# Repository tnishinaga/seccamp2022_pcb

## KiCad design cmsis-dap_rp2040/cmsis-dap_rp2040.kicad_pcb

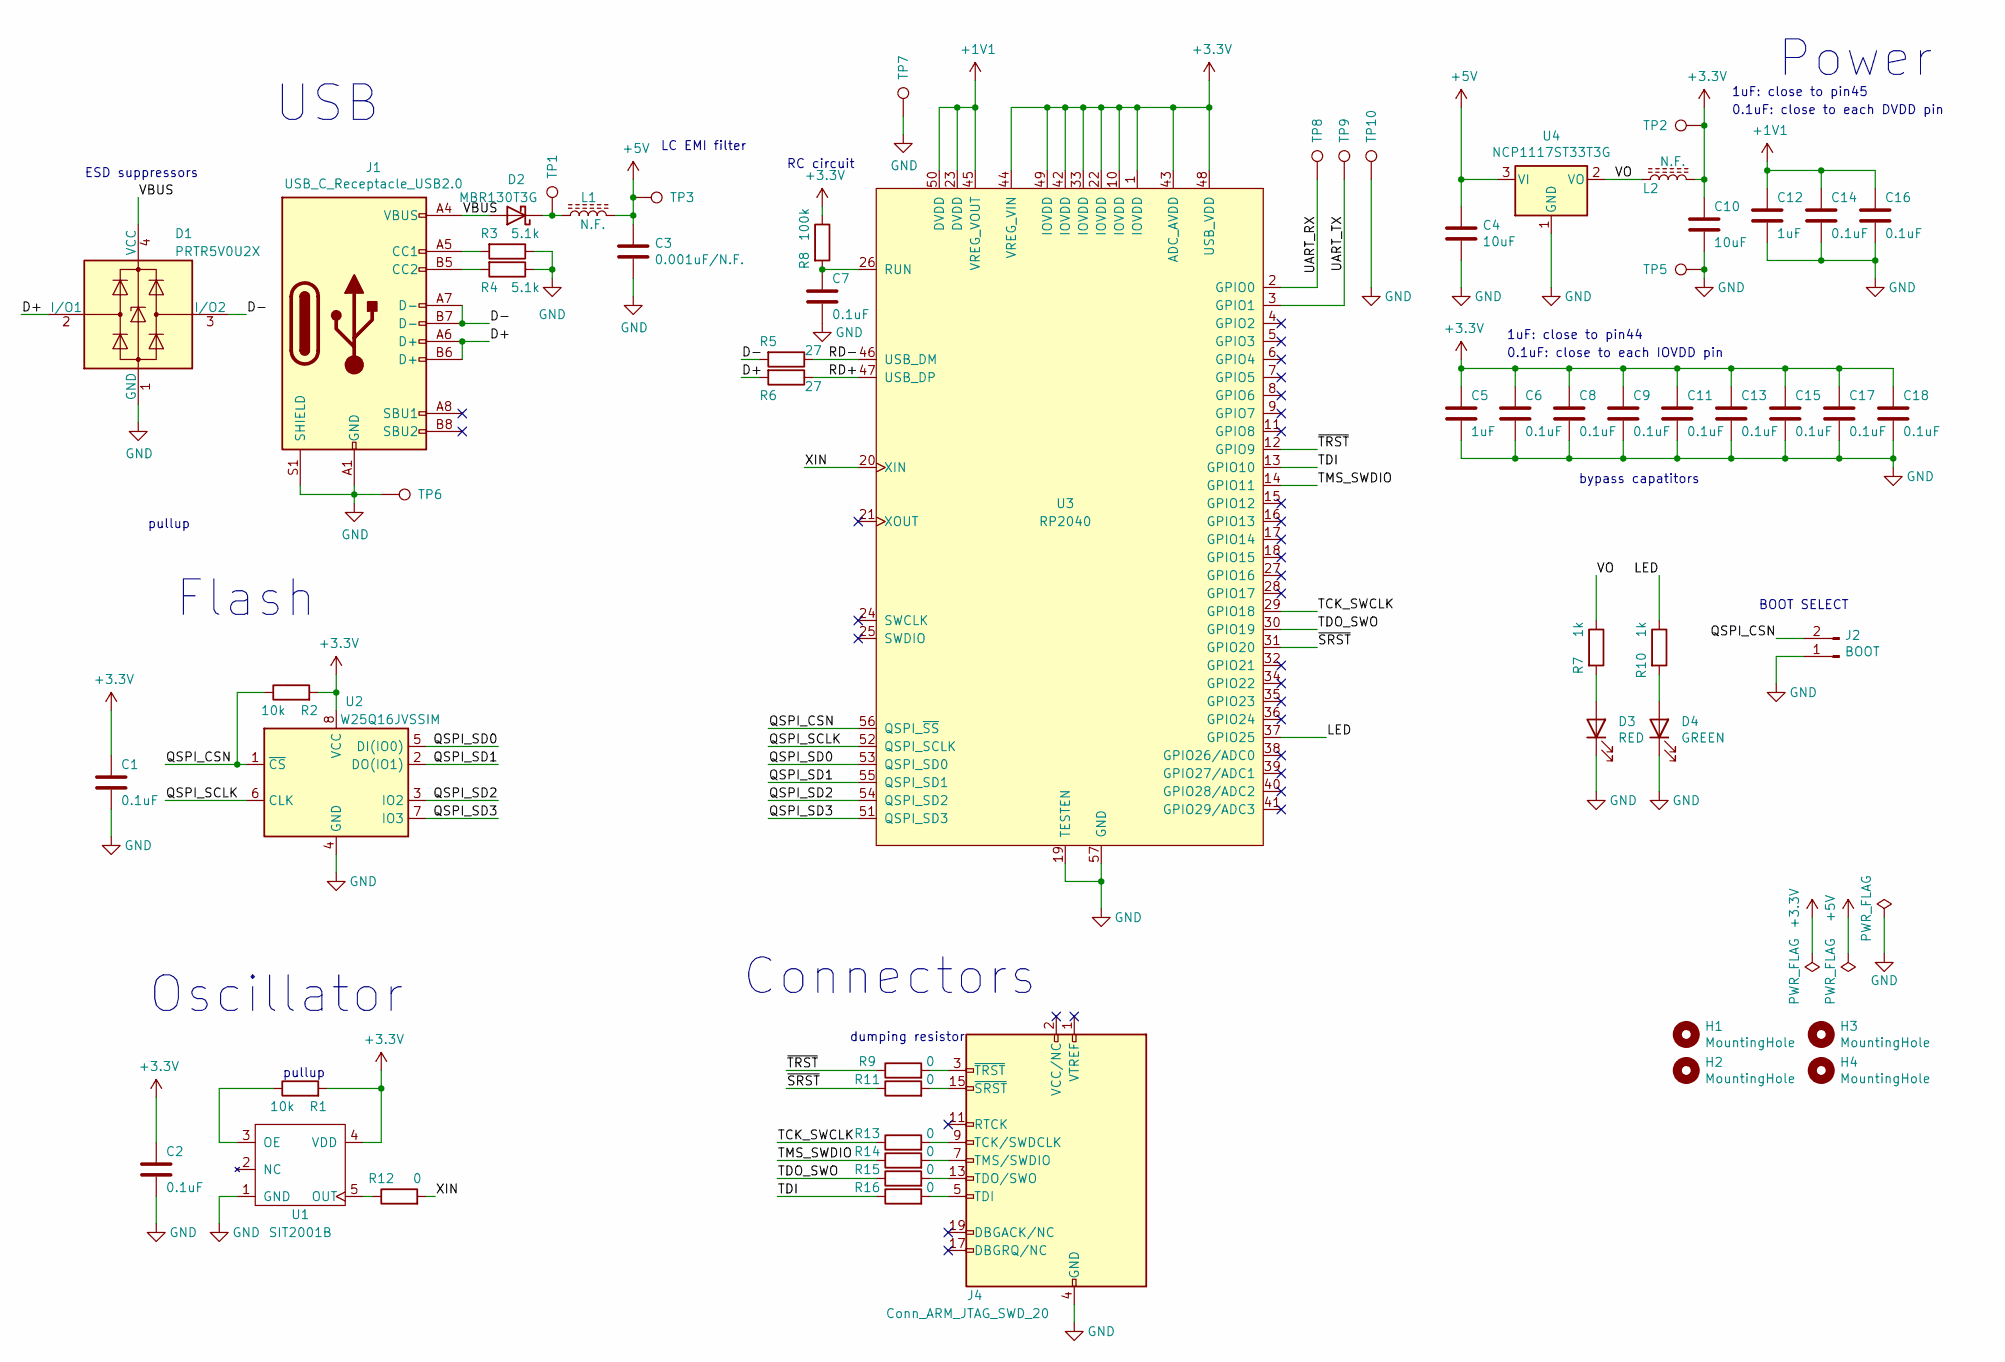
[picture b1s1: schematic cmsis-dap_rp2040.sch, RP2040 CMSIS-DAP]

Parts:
C1, C2, C6, C7, C8, C9, C11, C13, C14, C15, C16, C17, C18: 0.1uF; C_0603_1608Metric; MPN C1608X7R1E104M080AA
C3: 0.001uF/N.F.; C_0603_1608Metric; MPN CL10C102JB8NNND
C4, C10: 10uF; C_0603_1608Metric; MPN CL10A106MQ8NNNC
C5, C12: 1uF; C_0603_1608Metric; MPN C0603C105K8PACTU
D1: PRTR5V0U2X; SOT-143; MPN PRTR5V0U2X
D2: MBR130T3G; D_SOD-123F; MPN MBR130T3G
D3: RED; D_0603_1608Metric; MPN OSR50603C1E
D4: GREEN; D_0603_1608Metric; MPN OSG50603C1E
H1, H2, H3, H4: MountingHole; MountingHole_3mm
J1: USB_C_Receptacle_USB2.0; USB_C_Receptacle_GCT_USB4085; MPN USB4085-GF-A
J2: BOOT; PinHeader_1x02_P2.54mm_Vertical
J4: Conn_ARM_JTAG_SWD_20; IDC-Header_2x10_P2.54mm_Vertical
L1, L2: N.F.; L_0603_1608Metric; MPN BLM18AG601SN1D
R1, R2: 10k; R_0603_1608Metric; MPN ERJ-3EKF1002V
R3, R4: 5.1k; R_0603_1608Metric; MPN ERJ-3EKF5101V
R5, R6: 27; R_0603_1608Metric; MPN ERJ-3EKF27R0V
R7, R10: 1k; R_0603_1608Metric; MPN RC0603FR-131KL
R8: 100k; R_0603_1608Metric; MPN RC0603FR-10100KL
R9, R11, R12, R13, R14, R15, R16: 0; R_0603_1608Metric; MPN RK73Z1JTTD
TP1, TP2, TP3, TP5, TP6, TP7, TP8, TP9, TP10: TestPoint; TestPoint_Pad_D1.0mm
U1: SIT2001B; SOT-23-5; MPN SIT2001B
U2: W25Q16JVSSIM; SOIC-8_5.23x5.23mm_P1.27mm
U3: RP2040; RP2040_QFN56_HandSolderHack; MPN RP2040
U4: NCP1117ST33T3G; SOT-223-3_TabPin2; MPN NCP1117ST33T3G

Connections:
+1V1: C12.1, C14.1, C16.1, U3.23 (DVDD), U3.45 (VREG_VOUT), U3.50 (DVDD)
+3V3: C1.1, C2.1, C5.1, C6.1, C8.1, C9.1, C10.1, C11.1, C13.1, C15.1, C17.1, C18.1, L2.2, R1.2, R2.2, R8.1, TP2.1, U1.4 (VDD), U2.8 (VCC), U3.1 (IOVDD), U3.10 (IOVDD), U3.22 (IOVDD), U3.33 (IOVDD), U3.42 (IOVDD), U3.43 (ADC_AVDD), U3.44 (VREG_VIN), U3.48 (USB_VDD), U3.49 (IOVDD)
+5V: C3.1, C4.1, L1.2, TP3.1, U4.3 (VI)
/D+: D1.2 (I/O1), J1.A6 (D+), J1.B6 (D+), R6.2
/D-: D1.3 (I/O2), J1.A7 (D-), J1.B7 (D-), R5.2
/LED: R10.1, U3.37 (GPIO25)
/QSPI_CSN: J2.2, R2.1, U2.1 (~CS), U3.56 (QSPI_~SS)
/QSPI_SCLK: U2.6 (CLK), U3.52 (QSPI_SCLK)
/QSPI_SD0: U2.5 (DI(IO0)), U3.53 (QSPI_SD0)
/QSPI_SD1: U2.2 (DO(IO1)), U3.55 (QSPI_SD1)
/QSPI_SD2: U2.3 (IO2), U3.54 (QSPI_SD2)
/QSPI_SD3: U2.7 (IO3), U3.51 (QSPI_SD3)
/RD+: R6.1, U3.47 (USB_DP)
/RD-: R5.1, U3.46 (USB_DM)
/TCK_SWCLK: R13.1, U3.29 (GPIO18)
/TDI: R16.1, U3.13 (GPIO10)
/TDO_SWO: R15.1, U3.30 (GPIO19)
/TMS_SWDIO: R14.1, U3.14 (GPIO11)
/UART_RX: TP8.1, U3.2 (GPIO0)
/UART_TX: TP9.1, U3.3 (GPIO1)
/VBUS: D1.4 (VCC), D2.2 (A), J1.A4 (VBUS), J1.A9 (VBUS), J1.B4 (VBUS), J1.B9 (VBUS)
/VO: L2.1, R7.1, U4.2 (VO)
/XIN: R12.2, U3.20 (XIN)
/~SRST: R11.1, U3.31 (GPIO20)
/~TRST: R9.1, U3.12 (GPIO9)
GND: C1.2, C2.2, C3.2, C4.2, C5.2, C6.2, C7.2, C8.2, C9.2, C10.2, C11.2, C12.2, C13.2, C14.2, C15.2, C16.2, C17.2, C18.2, D1.1 (GND), D3.1 (K), D4.1 (K), J1.A1 (GND), J1.A12 (GND), J1.B1 (GND), J1.B12 (GND), J1.S1 (SHIELD), J2.1, J4.4 (GND), J4.6 (GND), J4.8 (GND), J4.10 (GND), J4.12 (GND), J4.14 (GND), J4.16 (GND), J4.18 (GND), J4.20 (GND), R3.1, R4.1, TP5.1, TP6.1, TP7.1, TP10.1, U1.1 (GND), U2.4 (GND), U3.19 (TESTEN), U3.57 (GND), U4.1 (GND)
unnamed: C7.1, R8.2, U3.26 (RUN)
unnamed: D2.1 (K), L1.1, TP1.1
unnamed: D3.2 (A), R7.2
unnamed: D4.2 (A), R10.2
unnamed: J1.A5 (CC1), R3.2
unnamed: J1.B5 (CC2), R4.2
unnamed: J4.3 (~TRST~), R9.2
unnamed: J4.5 (TDI), R16.2
unnamed: J4.7 (TMS/SWDIO), R14.2
unnamed: J4.9 (TCK/SWDCLK), R13.2
unnamed: J4.13 (TDO/SWO), R15.2
unnamed: J4.15 (~SRST~), R11.2
unnamed: R1.1, U1.3 (OE)
unnamed: R12.1, U1.5 (OUT)

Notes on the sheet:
1uF: close to pin44
0.1uF: close to each IOVDD pin
1uF: close to pin45
0.1uF: close to each DVDD pin
Power
Connectors
USB
Flash
Oscillator
RC circuit
pullup
bypass capatitors
dumping resistor
ESD suppressors
LC EMI filter
BOOT SELECT

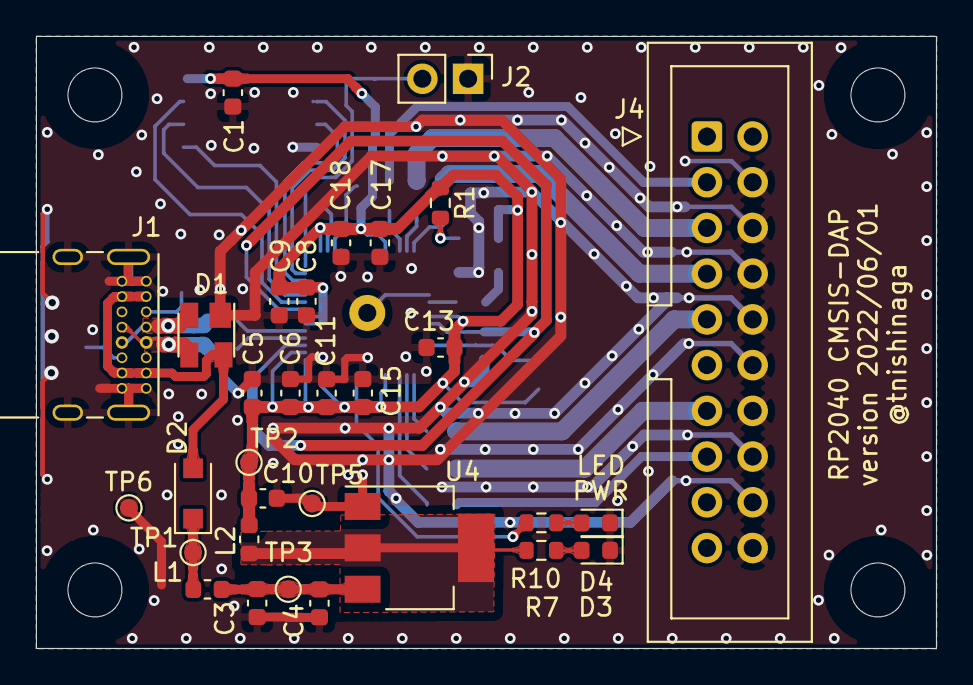
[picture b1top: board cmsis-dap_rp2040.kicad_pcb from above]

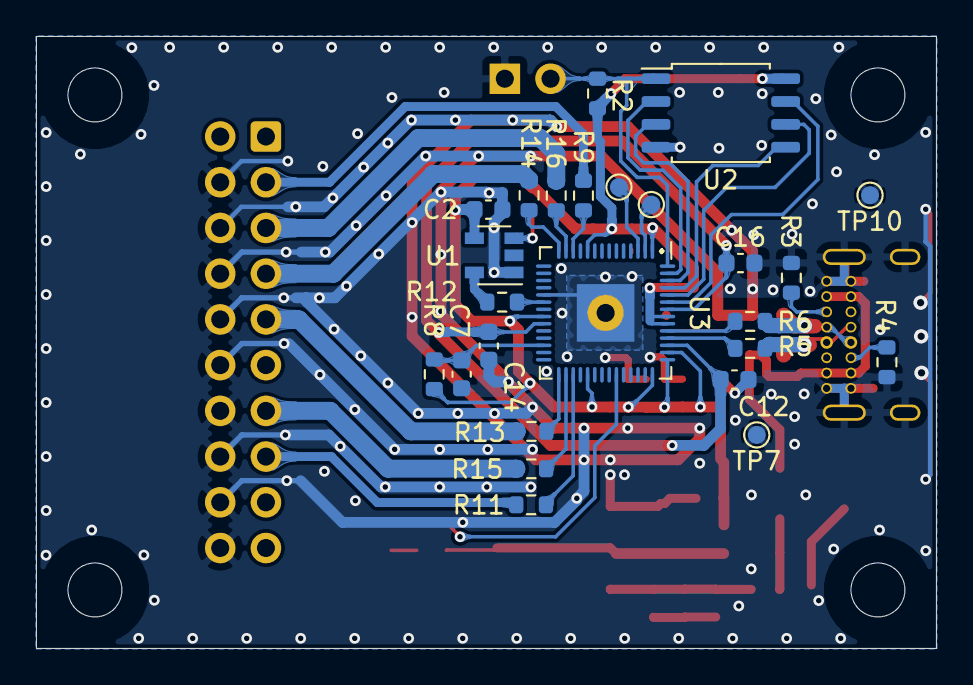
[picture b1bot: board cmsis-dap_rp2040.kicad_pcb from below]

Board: 2 copper layers, 50.0 x 34.0 mm, 60 parts (25 on the bottom side), 40 nets.

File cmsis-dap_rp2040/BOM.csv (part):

"Source:","/Users/tnishinaga/projects/tnishinaga/seccamp2022_pcb/cmsis-dap_rp2040/cmsis-dap_rp2040.sch"
"Date:","Friday, 15 April 2022 at 02:58:07"
"Tool:","Eeschema (5.1.10-1-10_14)"
"Generator:","/Applications/KiCad//kicad.app/Contents/SharedSupport/plugins/bom_csv_grouped_by_value.py"
"Component Count:","54"

"Individual Components:"

"Item","Qty","Reference(s)","Value","LibPart","Footprint","Datasheet","MPN"
"","","C1","0.1uF","Device:C","Capacitor_SMD:C_0603_1608Metric","~","C1608X7R1E104M080AA"
"","","C2","0.1uF","Device:C","Capacitor_SMD:C_0603_1608Metric","~","C1608X7R1E104M080AA"
"","","C3","0.001uF/N.F.","Device:C","Capacitor_SMD:C_0603_1608Metric","~","CL10C102JB8NNND"
"","","C4","10uF","Device:C","Capacitor_SMD:C_0603_1608Metric","~","CL10A106MQ8NNNC"
"","","C5","1uF","Device:C","Capacitor_SMD:C_0603_1608Metric","~","C0603C105K8PACTU"
"","","C6","0.1uF","Device:C","Capacitor_SMD:C_0603_1608Metric","~","C1608X7R1E104M080AA"
"","","C7","0.1uF","Device:C","Capacitor_SMD:C_0603_1608Metric","~","C1608X7R1E104M080AA"
"","","C8","0.1uF","Device:C","Capacitor_SMD:C_0603_1608Metric","~","C1608X7R1E104M080AA"
"","","C9","0.1uF","Device:C","Capacitor_SMD:C_0603_1608Metric","~","C1608X7R1E104M080AA"
"","","C10","10uF","Device:C","Capacitor_SMD:C_0603_1608Metric","~","CL10A106MQ8NNNC"
"","","C11","0.1uF","Device:C","Capacitor_SMD:C_0603_1608Metric","~","C1608X7R1E104M080AA"
"","","C12","1uF","Device:C","Capacitor_SMD:C_0603_1608Metric","~","C0603C105K8PACTU"
"","","C13","0.1uF","Device:C","Capacitor_SMD:C_0603_1608Metric","~","C1608X7R1E104M080AA"
"","","C14","0.1uF","Device:C","Capacitor_SMD:C_0603_1608Metric","~","C1608X7R1E104M080AA"
"","","C15","0.1uF","Device:C","Capacitor_SMD:C_0603_1608Metric","~","C1608X7R1E104M080AA"
"","","C16","0.1uF","Device:C","Capacitor_SMD:C_0603_1608Metric","~","C1608X7R1E104M080AA"
"","","C17","0.1uF","Device:C","Capacitor_SMD:C_0603_1608Metric","~","C1608X7R1E104M080AA"
"","","C18","0.1uF","Device:C","Capacitor_SMD:C_0603_1608Metric","~","C1608X7R1E104M080AA"
"","","D1","PRTR5V0U2X","Power_Protection:PRTR5V0U2X","Package_TO_SOT_SMD:SOT-143","https://assets.nexperia.com/documents/data-sheet/PRTR5V0U2X.pdf","PRTR5V0U2X"
"","","D2","MBR130T3G","Device:D_Schottky","Diode_SMD:D_SOD-123F","~","MBR130T3G"
"","","D3","RED","Device:LED","Diode_SMD:D_0603_1608Metric","~","OSR50603C1E"
"","","D4","GREEN","Device:LED","Diode_SMD:D_0603_1608Metric","~","OSG50603C1E"
"","","H1","MountingHole","Mechanical:MountingHole","MountingHole:MountingHole_3mm","~",""
"","","H2","MountingHole","Mechanical:MountingHole","MountingHole:MountingHole_3mm","~",""
"","","H3","MountingHole","Mechanical:MountingHole","MountingHole:MountingHole_3mm","~",""
"","","H4","MountingHole","Mechanical:MountingHole","MountingHole:MountingHole_3mm","~",""
"","","J1","USB_C_Receptacle_USB2.0","Connector:USB_C_Receptacle_USB2.0","Connector_USB:USB_C_Receptacle_GCT_USB4085","https://www.usb.org/sites/default/files/documents/usb_type-c.zip","USB4085-GF-A"
"","","J2","UART","Connector:Conn_01x04_Male","Connector_PinHeader_2.54mm:PinHeader_1x04_P2.54mm_Vertical","~",""
"","","J3","RP2040_SWD","Connector:Conn_01x03_Male","Connector_PinHeader_2.54mm:PinHeader_1x03_P2.54mm_Vertical","~",""
"","","J4","Conn_ARM_JTAG_SWD_20","Connector:Conn_ARM_JTAG_SWD_20","Connector_IDC:IDC-Header_2x10_P2.54mm_Vertical","http://infocenter.arm.com/help/topic/com.arm.doc.dui0499b/DU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",""
"","","L1","600R/0.5A/N.F.","Device:L_Core_Ferrite","Inductor_SMD:L_0603_1608Metric","~","BLM18AG601SN1D"
"","","L2","600R/0.5A","Device:L_Core_Ferrite","Inductor_SMD:L_0603_1608Metric","~","BLM18AG601SN1D"
"","","R1","10k","Device:R","Resistor_SMD:R_0603_1608Metric","~","ERJ-3EKF1002V"
"","","R2","10k","Device:R","Resistor_SMD:R_0603_1608Metric","~","ERJ-3EKF1002V"
"","","R3","5.1k","Device:R","Resistor_SMD:R_0603_1608Metric","~","ERJ-3EKF5101V"
"","","R4","5.1k","Device:R","Resistor_SMD:R_0603_1608Metric","~","ERJ-3EKF5101V"
"","","R5","27","Device:R","Resistor_SMD:R_0603_1608Metric","~","ERJ-3EKF27R0V"
"","","R6","27","Device:R","Resistor_SMD:R_0603_1608Metric","~","ERJ-3EKF27R0V"
"","","R7","1k","Device:R","Resistor_SMD:R_0603_1608Metric","~","RC0603FR-131KL"
"","","R8","100k","Device:R","Resistor_SMD:R_0603_1608Metric","~","RC0603FR-10100KL"
"","","R9","0","Device:R","Resistor_SMD:R_0603_1608Metric","~","RK73Z1JTTD"
"","","R10","1k","Device:R","Resistor_SMD:R_0603_1608Metric","~","RC0603FR-131KL"
"","","R11","0","Device:R","Resistor_SMD:R_0603_1608Metric","~","RK73Z1JTTD"
"","","R12","0","Device:R","Resistor_SMD:R_0603_1608Metric","~","RK73Z1JTTD"
"","","R13","0","Device:R","Resistor_SMD:R_0603_1608Metric","~","RK73Z1JTTD"
"","","R14","0","Device:R","Resistor_SMD:R_0603_1608Metric","~","RK73Z1JTTD"
"","","R15","0","Device:R","Resistor_SMD:R_0603_1608Metric","~","RK73Z1JTTD"
"","","R16","0","Device:R","Resistor_SMD:R_0603_1608Metric","~","RK73Z1JTTD"
"","","SW1","BOOT","Switch:SW_Push","Button_Switch_SMD:SW_Push_SPST_NO_Alps_SKRK","~","SKRKAHE020"
"","","SW2","RUN","Switch:SW_Push","Button_Switch_SMD:SW_Push_SPST_NO_Alps_SKRK","~","SKRKAHE020"
"","","U1","SIT2001B","sit2001:SIT2001B","Package_TO_SOT_SMD:SOT-23-5","","SIT2001B"
"","","U2","W25Q16JVSSIM","Memory_Flash:W25Q32JVSS","Package_SO:SOIC-8_5.23x5.23mm_P1.27mm","http://www.winbond.com/resource-files/w25q32jv%20revg%200327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",""
"","","U3","RP2040","rp2040:RP2040","Package_DFN_QFN:QFN-56-1EP_7x7mm_P0.4mm_EP5.6x5.6mm","","RP2040"
"","","U4","NCP1117ST33T3G","Regulator_Linear:NCP1117-3.3_SOT223","Package_TO_SOT_SMD:SOT-223-3_TabPin2","http://www.onsemi.com/pub_link/Collateral/NCP1117-D.PDF","NCP1117ST33T3G"



"Collated Components:"

"Item","Qty","Reference(s)","Value","LibPart","Footprint","Datasheet","MPN"
"1","13","C1, C2, C6, C7, C8, C9, C11, C13, C14, C15, C16, C17, C18","0.1uF","Device:C","Capacitor_SMD:C_0603_1608Metric","~","C1608X7R1E104M080AA"
"2","1","C3","0.001uF/N.F.","Device:C","Capacitor_SMD:C_0603_1608Metric","~","CL10C102JB8NNND"
"3","2","C4, C10","10uF","Device:C","Capacitor_SMD:C_0603_1608Metric","~","CL10A106MQ8NNNC"
"4","2","C5, C12","1uF","Device:C","Capacitor_SMD:C_0603_1608Metric","~","C0603C105K8PACTU"
"5","1","D1","PRTR5V0U2X","Power_Protection:PRTR5V0U2X","Package_TO_SOT_SMD:SOT-143","https://assets.nexperia.com/documents/data-sheet/PRTR5V0U2X.pdf","PRTR5V0U2X"
"6","1","D2","MBR130T3G","Device:D_Schottky","Diode_SMD:D_SOD-123F","~","MBR130T3G"
"7","1","D3","RED","Device:LED","Diode_SMD:D_0603_1608Metric","~","OSR50603C1E"
"8","1","D4","GREEN","Device:LED","Diode_SMD:D_0603_1608Metric","~","OSG50603C1E"
"9","4","H1, H2, H3, H4","MountingHole","Mechanical:MountingHole","MountingHole:MountingHole_3mm","~",""
"10","1","J1","USB_C_Receptacle_USB2.0","Connector:USB_C_Receptacle_USB2.0","Connector_USB:USB_C_Receptacle_GCT_USB4085","https://www.usb.org/sites/default/files/documents/usb_type-c.zip","USB4085-GF-A"
"11","1","J2","UART","Connector:Conn_01x04_Male","Connector_PinHeader_2.54mm:PinHeader_1x04_P2.54mm_Vertical","~",""
"12","1","J3","RP2040_SWD","Connector:Conn_01x03_Male","Connector_PinHeader_2.54mm:PinHeader_1x03_P2.54mm_Vertical","~",""
"13","1","J4","Conn_ARM_JTAG_SWD_20","Connector:Conn_ARM_JTAG_SWD_20","Connector_IDC:IDC-Header_2x10_P2.54mm_Vertical","http://infocenter.arm.com/help/topic/com.arm.doc.dui0499b/DU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",""
"14","1","L1","600R/0.5A/N.F.","Device:L_Core_Ferrite","Inductor_SMD:L_0603_1608Metric","~","BLM18AG601SN1D"
"15","1","L2","600R/0.5A","Device:L_Core_Ferrite","Inductor_SMD:L_0603_1608Metric","~","BLM18AG601SN1D"
"16","2","R1, R2","10k","Device:R","Resistor_SMD:R_0603_1608Metric","~","ERJ-3EKF1002V"
"17","2","R3, R4","5.1k","Device:R","Resistor_SMD:R_0603_1608Metric","~","ERJ-3EKF5101V"
"18","2","R5, R6","27","Device:R","Resistor_SMD:R_0603_1608Metric","~","ERJ-3EKF27R0V"
"19","2","R7, R10","1k","Device:R","Resistor_SMD:R_0603_1608Metric","~","RC0603FR-131KL"
"20","1","R8","100k","Device:R","Resistor_SMD:R_0603_1608Metric","~","RC0603FR-10100KL"
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
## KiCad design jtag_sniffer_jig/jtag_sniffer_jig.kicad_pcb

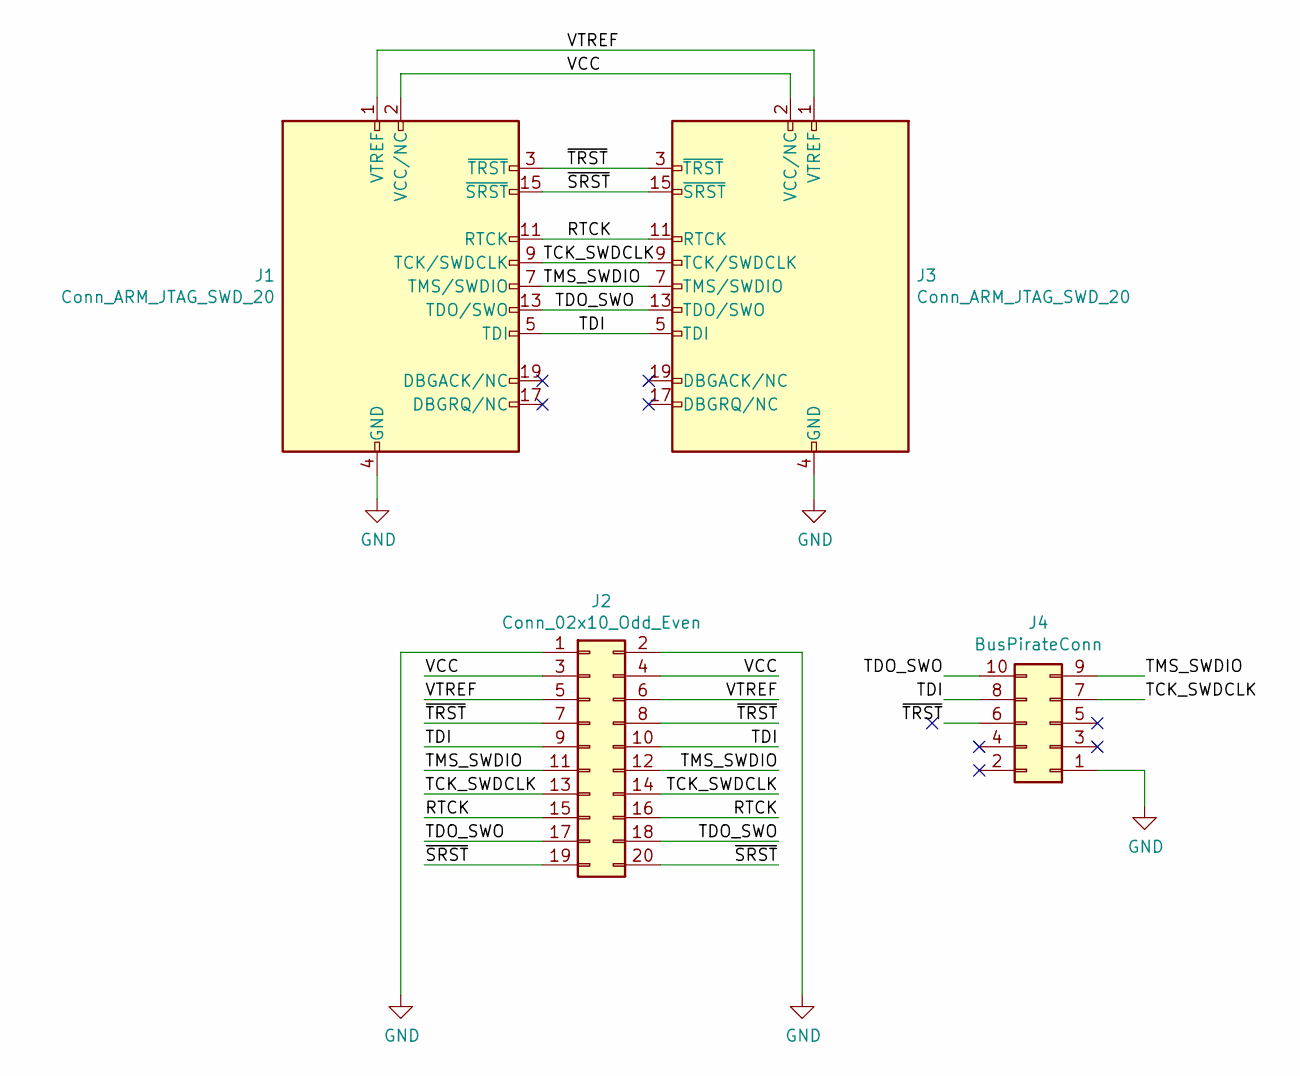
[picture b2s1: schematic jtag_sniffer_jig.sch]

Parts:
J1: Conn_ARM_JTAG_SWD_20; PinSocket_2x10_P2.54mm_Horizontal
J2: Conn_02x10_Odd_Even; PinHeader_2x10_P2.54mm_Vertical
J3: Conn_ARM_JTAG_SWD_20; IDC-Header_2x10_P2.54mm_Horizontal
J4: BusPirateConn; IDC-Header_2x05_P2.54mm_Vertical

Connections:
/RTCK: J1.11 (RTCK), J2.15, J2.16, J3.11 (RTCK)
/TCK_SWDCLK: J1.9 (TCK/SWDCLK), J2.13, J2.14, J3.9 (TCK/SWDCLK), J4.7
/TDI: J1.5 (TDI), J2.9, J2.10, J3.5 (TDI), J4.8
/TDO_SWO: J1.13 (TDO/SWO), J2.17, J2.18, J3.13 (TDO/SWO), J4.10
/TMS_SWDIO: J1.7 (TMS/SWDIO), J2.11, J2.12, J3.7 (TMS/SWDIO), J4.9
/VCC: J1.2 (VCC/NC), J2.3, J2.4, J3.2 (VCC/NC)
/VTREF: J1.1 (VTREF), J2.5, J2.6, J3.1 (VTREF)
/~SRST: J1.15 (~SRST~), J2.19, J2.20, J3.15 (~SRST~)
/~TRST: J1.3 (~TRST~), J2.7, J2.8, J3.3 (~TRST~), J4.6
GND: J1.4 (GND), J1.6 (GND), J1.8 (GND), J1.10 (GND), J1.12 (GND), J1.14 (GND), J1.16 (GND), J1.18 (GND), J1.20 (GND), J2.1, J2.2, J3.4 (GND), J3.6 (GND), J3.8 (GND), J3.10 (GND), J3.12 (GND), J3.14 (GND), J3.16 (GND), J3.18 (GND), J3.20 (GND), J4.1

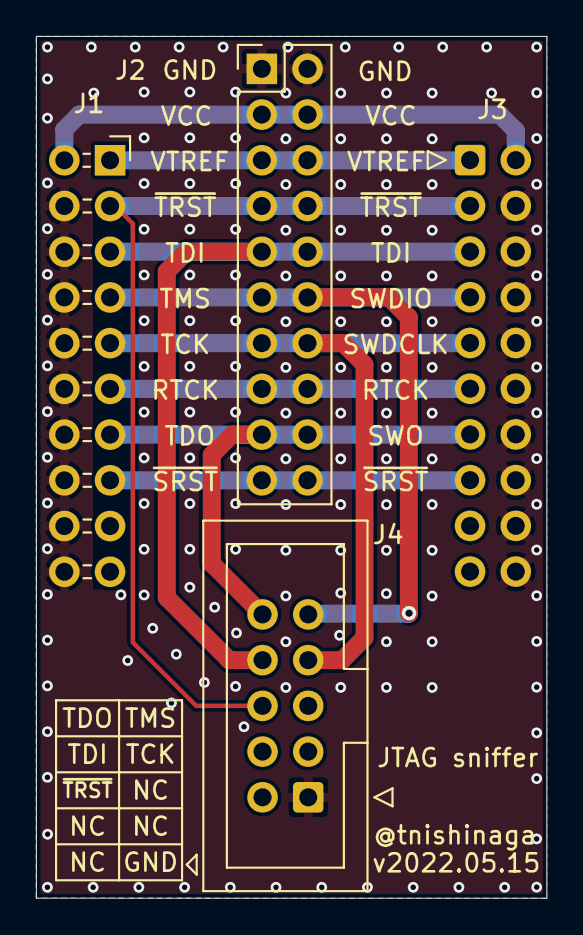
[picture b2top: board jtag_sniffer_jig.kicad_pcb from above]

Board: 2 copper layers, 28.4 x 47.9 mm, 4 parts (0 on the bottom side), 10 nets.

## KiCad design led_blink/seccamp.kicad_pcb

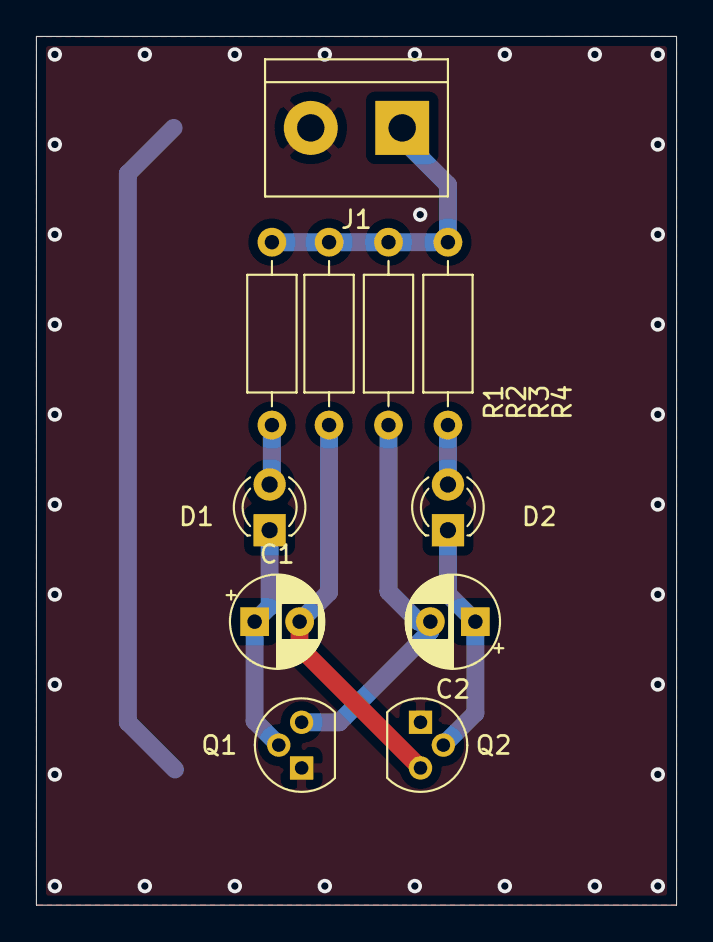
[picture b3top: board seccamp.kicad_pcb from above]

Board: 2 copper layers, 35.6 x 48.3 mm, 11 parts (0 on the bottom side), 8 nets.

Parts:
C1, C2: 100uF; CP_Radial_D5.0mm_P2.50mm
D1, D2: LED; LED_D3.0mm
J1: Screw_Terminal_01x02; TerminalBlock_bornier-2_P5.08mm
Q1, Q2: 2SC1815; TO-92
R1, R4: 100; R_Axial_DIN0207_L6.3mm_D2.5mm_P10.16mm_Horizontal
R2, R3: 10k; R_Axial_DIN0207_L6.3mm_D2.5mm_P10.16mm_Horizontal

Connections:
GND: J1.2, Q1.1, Q2.1
unnamed: C1.1, D1.1, Q1.2
unnamed: C1.2, Q2.3, R2.2
unnamed: C2.1, D2.1, Q2.2
unnamed: C2.2, Q1.3, R3.2
unnamed: D1.2, R1.2
unnamed: D2.2, R4.2
VCC: J1.1, R1.1, R2.1, R3.1, R4.1

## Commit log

2022-04-14 Release v2022-04-09
2022-06-05 Release v2022.06.01
2022-06-17 update files
